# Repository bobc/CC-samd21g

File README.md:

CC-samd21g Breakout Board
========================================

The CC-SAMD21 Breakout Board is breakout for the Atmel ATSAMD21G18 with prototyping area.  
This board shape is dirfferent from Arduino UNO or Zero, but it has Arduino Uno V3 style headers.  
There are only the minimal set of parts for running microcontroller. When you make your own circuit boards, this board might be helpful.

### Some highlights of the CC-samd21g Breakout Board:
 1. Main core: [ATSAMD21G18](http://www.atmel.com/devices/ATSAMD21G18A.aspx)
 2. Volatage regulator can be mounted in the extra prototyping area.
 3. Prototyping area 43.94mm(1730mil) x 53.34mm(2100mil)
 4. Measures 99.82mm(3930mil) x 53.34mm(2100mil)

Repository Contents
-------------------
* **/Hardware** - All Eagle design files (.brd, .sch)
* **/Software** - Software files for this hardware

Description(Pin Interfaces)
-------------------

### CN1 Pin Descriptions:
This connector is for Flashing a program microcontroller.
If you change BOOT MODE, To be selected BOOT MODE before connecting the power supply.  
And also, Communicate with SMA21G using "Serial" function.
- **VCC:** Restrictly 3.3VDC.
- **TX:** PB22 used as UART TX.
- **RX:** PB23 used as UART RX.
- **GND:** GND.
- **BOOT MODE:** Connected to "PA13" H:Flash boot(normally) L:UART download

If you are interested in more useful uart module, please see the [General Serial Communication Board](https://github.com/NaoNaoMe/General-Serial-Communication-Board).

### CN2 Pin Descriptions:
This connector is as power supply.
You can mount a voltage regulator in the extra prototyping area near the connector.
- **VIN:** Depending on the voltage regulator requirements.
- **GND:** GND.

How to burn bootloader and upload sketch
-------------------
See [this page](BurnBootloader.md)

License
-------------------
The repository is released under [Creative Commons ShareAlike 4.0 International](https://creativecommons.org/licenses/by-sa/4.0/).

Distributed as-is; no warranty is given.

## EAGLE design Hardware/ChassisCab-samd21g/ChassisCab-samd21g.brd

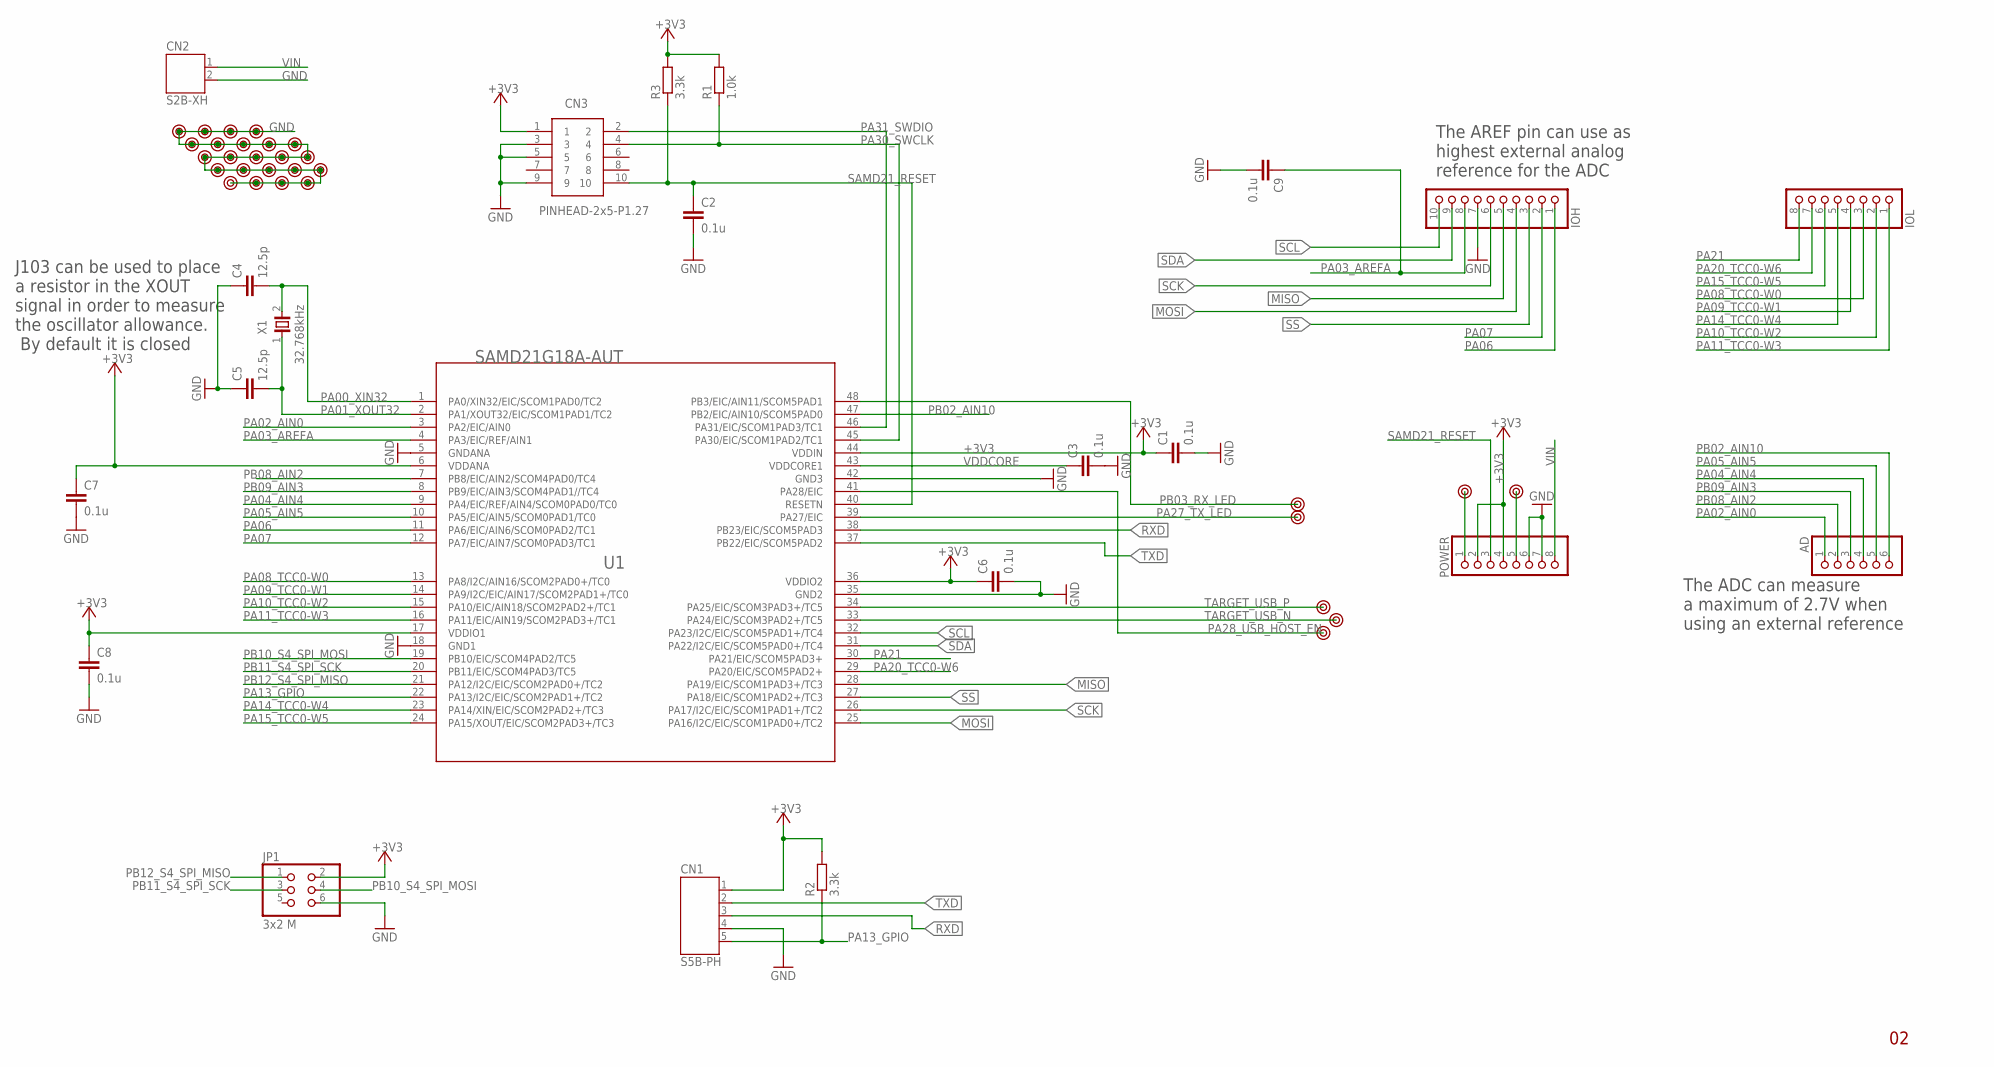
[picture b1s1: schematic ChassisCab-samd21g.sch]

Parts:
AD: 6x1F-H8.5; 1X06
C1, C2, C3, C6, C7, C8, C9: 0.1u; C0603
C4, C5: 12.5p; C0603
CN1: S5B-PH
CN2: S2B-XH
CN3: PINHEAD-2x5-P1.27; SHF-105-01-X-D-SM
IOH: 10x1F-H8.5; 1X10
IOL: 8x1F-H8.5; 1X08
JP1: 3x2 M; 2X03
POWER: 8x1F-H8.5; 1X08
R1: 1.0k; R0603
R2, R3: 3.3k; R0603
U1: SAMD21G18A-AUT; TQFP48
U$1, U$2, U$3, U$4, U$6, U$7, U$8, U$9, U$10, U$11, U$12, U$13, U$14, U$15, U$16, U$17, U$18, U$19, U$20, U$21, U$22, U$23, U$24, U$25, U$26, U$27, U$28, U$29, U$30, U$31: PAD
X1: 32.768kHz; FC-135

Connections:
+3V3: C1.1, C6.1, C7.1, C8.1, CN1.1, CN3.1, JP1.2, POWER.2, POWER.4, R1.2, R2.2, R3.2, U1.6 (VDDANA), U1.17 (VDDIO1), U1.36 (VDDIO2), U1.44 (VDDIN)
GND: C1.2, C2.2, C3.2, C4.1, C5.1, C6.2, C7.2, C8.2, C9.2, CN1.4, CN2.2, CN3.3, CN3.5, CN3.9, IOH.7, JP1.6, POWER.6, POWER.7, U1.5 (GNDANA), U1.18 (GND1), U1.35 (GND2), U1.42 (GND3), U$2.1, U$8.1, U$9.1, U$10.1, U$11.1, U$12.1, U$13.1, U$14.1, U$15.1, U$16.1, U$17.1, U$18.1, U$19.1, U$20.1, U$21.1, U$22.1, U$23.1, U$24.1, U$25.1, U$26.1, U$27.1, U$28.1, U$31.1
MISO: IOH.5, U1.28 (PA19/EIC/SCOM1PAD3+/TC3)
MOSI: IOH.4, U1.25 (PA16/I2C/EIC/SCOM1PAD0+/TC2)
unnamed: POWER.1, U$29.1
unnamed: POWER.5, U$30.1
PA00_XIN32: C4.2, U1.1 (PA0/XIN32/EIC/SCOM1PAD0/TC2), X1.2
PA01_XOUT32: C5.2, U1.2 (PA1/XOUT32/EIC/SCOM1PAD1/TC2), X1.1
PA02_AIN0: AD.1, U1.3 (PA2/EIC/AIN0)
PA03_AREFA: C9.1, IOH.8, U1.4 (PA3/EIC/REF/AIN1)
PA04_AIN4: AD.4, U1.9 (PA4/EIC/REF/AIN4/SCOM0PAD0/TC0)
PA05_AIN5: AD.5, U1.10 (PA5/EIC/AIN5/SCOM0PAD1/TC0)
PA06: IOH.1, U1.11 (PA6/EIC/AIN6/SCOM0PAD2/TC1)
PA07: IOH.2, U1.12 (PA7/EIC/AIN7/SCOM0PAD3/TC1)
PA08_TCC0-W0: IOL.3, U1.13 (PA8/I2C/AIN16/SCOM2PAD0+/TC0)
PA09_TCC0-W1: IOL.4, U1.14 (PA9/I2C/EIC/AIN17/SCOM2PAD1+/TC0)
PA10_TCC0-W2: IOL.2, U1.15 (PA10/EIC/AIN18/SCOM2PAD2+/TC1)
PA11_TCC0-W3: IOL.1, U1.16 (PA11/EIC/AIN19/SCOM2PAD3+/TC1)
PA13_GPIO: CN1.5, R2.1, U1.22 (PA13/I2C/EIC/SCOM2PAD1+/TC2)
PA14_TCC0-W4: IOL.5, U1.23 (PA14/XIN/EIC/SCOM2PAD2+/TC3)
PA15_TCC0-W5: IOL.6, U1.24 (PA15/XOUT/EIC/SCOM2PAD3+/TC3)
PA20_TCC0-W6: IOL.7, U1.29 (PA20/EIC/SCOM5PAD2+)
PA21: IOL.8, U1.30 (PA21/EIC/SCOM5PAD3+)
PA27_TX_LED: U1.39 (PA27/EIC), U$4.1
PA28_USB_HOST_EN: U1.41 (PA28/EIC), U$3.1
PA30_SWCLK: CN3.4, R1.1, U1.45 (PA30/EIC/SCOM1PAD2/TC1)
PA31_SWDIO: CN3.2, U1.46 (PA31/EIC/SCOM1PAD3/TC1)
PB02_AIN10: AD.6, U1.47 (PB2/EIC/AIN10/SCOM5PAD0)
PB03_RX_LED: U1.48 (PB3/EIC/AIN11/SCOM5PAD1), U$1.1
PB08_AIN2: AD.2, U1.7 (PB8/EIC/AIN2/SCOM4PAD0/TC4)
PB09_AIN3: AD.3, U1.8 (PB9/EIC/AIN3/SCOM4PAD1//TC4)
PB10_S4_SPI_MOSI: JP1.4, U1.19 (PB10/EIC/SCOM4PAD2/TC5)
PB11_S4_SPI_SCK: JP1.3, U1.20 (PB11/EIC/SCOM4PAD3/TC5)
PB12_S4_SPI_MISO: JP1.1, U1.21 (PA12/I2C/EIC/SCOM2PAD0+/TC2)
RXD: CN1.3, U1.38 (PB23/EIC/SCOM5PAD3)
SAMD21_RESET: C2.1, CN3.10, POWER.3, R3.1, U1.40 (RESETN)
SCK: IOH.6, U1.26 (PA17/I2C/EIC/SCOM1PAD1+/TC2)
SCL: IOH.10, U1.32 (PA23/I2C/EIC/SCOM5PAD1+/TC4)
SDA: IOH.9, U1.31 (PA22/I2C/EIC/SCOM5PAD0+/TC4)
SS: IOH.3, U1.27 (PA18/EIC/SCOM1PAD2+/TC3)
TARGET_USB_N: U1.33 (PA24/EIC/SCOM3PAD2+/TC5), U$7.1
TARGET_USB_P: U1.34 (PA25/EIC/SCOM3PAD3+/TC5), U$6.1
TXD: CN1.2, U1.37 (PB22/EIC/SCOM5PAD2)
VDDCORE: C3.1, U1.43 (VDDCORE1)
VIN: CN2.1, POWER.8

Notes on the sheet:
J103 can be used to place a resistor in the XOUT signal in order to measure the oscillator allowance. By default it is closed
The ADC can measure a maximum of 2.7V when using an external reference
The AREF pin can use as highest external analog reference for the ADC

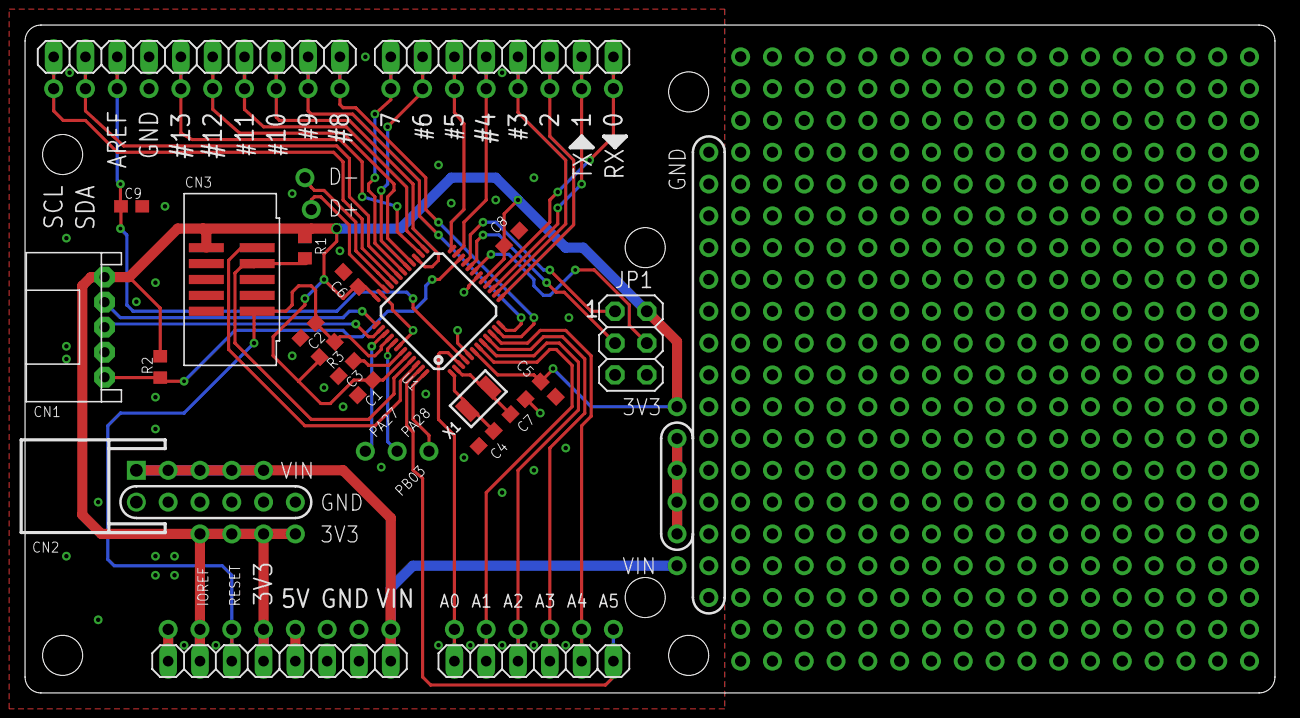
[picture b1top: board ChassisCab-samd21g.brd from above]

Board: 2 copper layers, 99.8 x 53.3 mm, 52 parts (0 on the bottom side), 45 nets.

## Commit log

2017-03-31 add files
2017-05-13 typo
2017-06-13 Conversion to KiCad

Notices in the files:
parts and their libraries:
jst: Copyright (C) 2016, Naoya Imai
